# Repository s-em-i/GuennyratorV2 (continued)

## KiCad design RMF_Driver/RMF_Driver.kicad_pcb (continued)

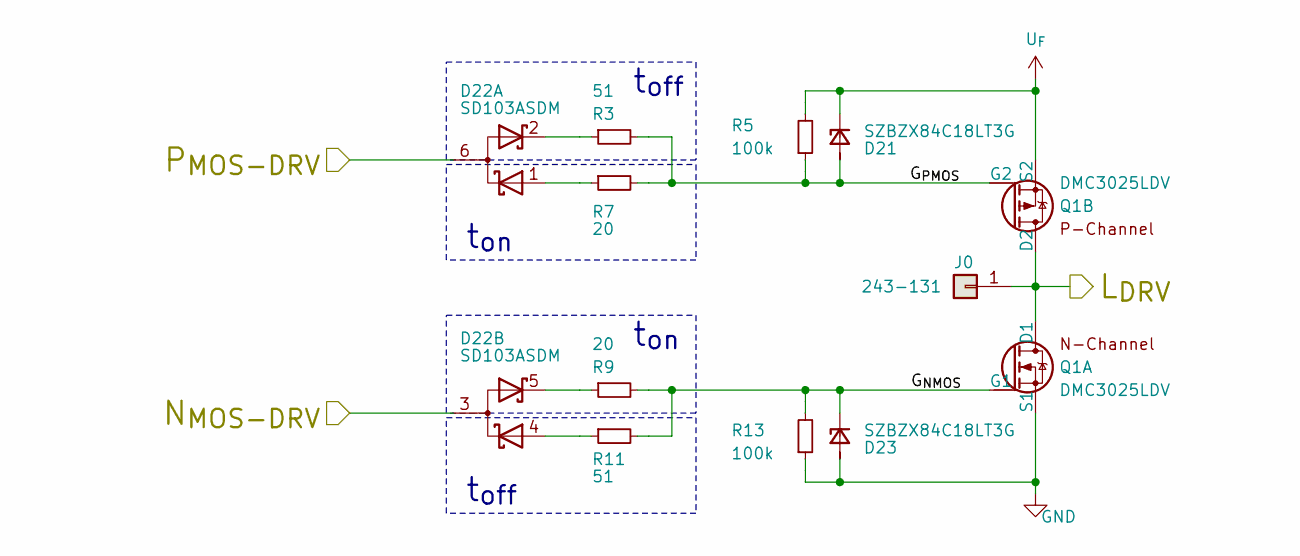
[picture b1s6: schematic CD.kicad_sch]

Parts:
D21, D23: SZBZX84C18LT3G; SOT-23; MPN 1 SZBZX84C18LT3G
D22: SD103ASDM; SOT-23-6; MPN 1 SD103ASDM-7-F
J0: 243-131; MPN 1 243-131
Q1: DMC3025LDV; Diodes_PowerDI3333-8_TypeUXC; MPN 1 DMC3025LDV
R3, R11: 51; R_0402_1005Metric; MPN 1 AC0402FR-0751RL
R5, R13: 100k; R_0402_1005Metric; MPN 1 AC0402FR-13100KL
R7, R9: 20; R_0402_1005Metric; MPN 1 AC0402FR-0720RL

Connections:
/Mosfet Coil Driver/CD1/G_{NMOS}: D23.3 (K), Q1.2 (G1), R9.2, R11.2, R13.2
/Mosfet Coil Driver/CD1/G_{PMOS}: D21.1 (A), D21.2 (A), Q1.4 (G2), R3.2, R5.1, R7.2
/Mosfet Coil Driver/CD1/N_{MOS-DRV}: D22.3 (AK2); also elsewhere on the board
/Mosfet Coil Driver/CD1/P_{MOS-DRV}: D22.6 (AK1); also elsewhere on the board
GND: D23.1 (A), D23.2 (A), Q1.1 (S1), R13.1; also elsewhere on the board
L_{0}-L_{1}: J0.1 (Pin_1_1), Q1.5 (D2), Q1.8 (D1)
unnamed: D22.1 (A1), R7.1
unnamed: D22.2 (K1), R3.1
unnamed: D22.4 (A1), R11.1
unnamed: D22.5 (K2), R9.1
U_{F}: D21.3 (K), Q1.3 (S2), R5.2; also elsewhere on the board

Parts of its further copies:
D24, D26, D27, D29, D30, D32, D33, D35, D36, D38, D39, D41, D42, D44, D45, D47, D48, D50, D51, D53, D54, D56, D57, D59, D60, D62, D63, D65, D66, D68, D69, D71, D72, D74: SZBZX84C18LT3G; SOT-23; MPN 1 SZBZX84C18LT3G
D25, D28, D31, D34, D37, D40, D43, D46, D49, D52, D55, D58, D61, D64, D67, D70, D73: SD103ASDM; SOT-23-6; MPN 1 SD103ASDM-7-F
J1, J2, J3, J4, J5, J6, J7, J8, J9, J10, J11, J12, J13, J14, J15, J16, J17: 243-131; MPN 1 243-131
Q0, Q2, Q3, Q4, Q5, Q6, Q7, Q8, Q9, Q10, Q11, Q12, Q13, Q14, Q15, Q16, Q17: DMC3025LDV; Diodes_PowerDI3333-8_TypeUXC; MPN 1 DMC3025LDV
R15, R23, R27, R35, R39, R43, R45, R49, R51, R55, R57, R61, R63, R67, R69, R73, R75, R79, R81, R85, R87, R91, R93, R97, R99, R103, R105, R109, R111, R115, R117, R121, R123, R127: 51; R_0402_1005Metric; MPN 1 AC0402FR-0751RL
R17, R25, R29, R37, R40, R44, R46, R50, R52, R56, R58, R62, R64, R68, R70, R74, R76, R80, R82, R86, R88, R92, R94, R98, R100, R104, R106, R110, R112, R116, R118, R122, R124, R128: 100k; R_0402_1005Metric; MPN 1 AC0402FR-13100KL
R19, R21, R31, R33, R41, R42, R47, R48, R53, R54, R59, R60, R65, R66, R71, R72, R77, R78, R83, R84, R89, R90, R95, R96, R101, R102, R107, R108, R113, R114, R119, R120, R125, R126: 20; R_0402_1005Metric; MPN 1 AC0402FR-0720RL

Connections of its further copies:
/Mosfet Coil Driver/CD0/G_{NMOS}: D26.3 (K), Q0.2 (G1), R21.2, R23.2, R25.2
/Mosfet Coil Driver/CD0/G_{PMOS}: D24.1 (A), D24.2 (A), Q0.4 (G2), R15.2, R17.1, R19.2
/Mosfet Coil Driver/CD0/N_{MOS-DRV}: D25.3 (AK2), D52.3 (AK2); also elsewhere on the board
/Mosfet Coil Driver/CD0/P_{MOS-DRV}: D25.6 (AK1), D52.6 (AK1); also elsewhere on the board
/Mosfet Coil Driver/CD1/N_{MOS-DRV}: D55.3 (AK2); also elsewhere on the board
/Mosfet Coil Driver/CD1/P_{MOS-DRV}: D55.6 (AK1); also elsewhere on the board
/Mosfet Coil Driver/CD2/G_{NMOS}: D29.3 (K), Q2.2 (G1), R33.2, R35.2, R37.2
/Mosfet Coil Driver/CD2/G_{PMOS}: D27.1 (A), D27.2 (A), Q2.4 (G2), R27.2, R29.1, R31.2
/Mosfet Coil Driver/CD3/G_{NMOS}: D32.3 (K), Q3.2 (G1), R42.2, R43.2, R44.2
/Mosfet Coil Driver/CD3/G_{PMOS}: D30.1 (A), D30.2 (A), Q3.4 (G2), R39.2, R40.1, R41.2
/Mosfet Coil Driver/CD4/G_{NMOS}: D35.3 (K), Q4.2 (G1), R48.2, R49.2, R50.2
/Mosfet Coil Driver/CD4/G_{PMOS}: D33.1 (A), D33.2 (A), Q4.4 (G2), R45.2, R46.1, R47.2
/Mosfet Coil Driver/CD5/G_{NMOS}: D38.3 (K), Q5.2 (G1), R54.2, R55.2, R56.2
/Mosfet Coil Driver/CD5/G_{PMOS}: D36.1 (A), D36.2 (A), Q5.4 (G2), R51.2, R52.1, R53.2
/Mosfet Coil Driver/CD6/G_{NMOS}: D41.3 (K), Q6.2 (G1), R60.2, R61.2, R62.2
/Mosfet Coil Driver/CD6/G_{PMOS}: D39.1 (A), D39.2 (A), Q6.4 (G2), R57.2, R58.1, R59.2
/Mosfet Coil Driver/CD7/G_{NMOS}: D44.3 (K), Q7.2 (G1), R66.2, R67.2, R68.2
/Mosfet Coil Driver/CD7/G_{PMOS}: D42.1 (A), D42.2 (A), Q7.4 (G2), R63.2, R64.1, R65.2
/Mosfet Coil Driver/CD8/G_{NMOS}: D47.3 (K), Q8.2 (G1), R72.2, R73.2, R74.2
/Mosfet Coil Driver/CD8/G_{PMOS}: D45.1 (A), D45.2 (A), Q8.4 (G2), R69.2, R70.1, R71.2
/Mosfet Coil Driver/CD9/G_{NMOS}: D53.3 (K), Q9.2 (G1), R84.2, R85.2, R86.2
/Mosfet Coil Driver/CD9/G_{PMOS}: D51.1 (A), D51.2 (A), Q9.4 (G2), R81.2, R82.1, R83.2
/Mosfet Coil Driver/CD10/G_{NMOS}: D56.3 (K), Q10.2 (G1), R90.2, R91.2, R92.2
/Mosfet Coil Driver/CD10/G_{PMOS}: D54.1 (A), D54.2 (A), Q10.4 (G2), R87.2, R88.1, R89.2
/Mosfet Coil Driver/CD11/G_{NMOS}: D50.3 (K), Q11.2 (G1), R78.2, R79.2, R80.2
/Mosfet Coil Driver/CD11/G_{PMOS}: D48.1 (A), D48.2 (A), Q11.4 (G2), R75.2, R76.1, R77.2
/Mosfet Coil Driver/CD11/N_{MOS-DRV}: D28.3 (AK2), D49.3 (AK2); also elsewhere on the board
/Mosfet Coil Driver/CD11/P_{MOS-DRV}: D28.6 (AK1), D49.6 (AK1); also elsewhere on the board
/Mosfet Coil Driver/CD12/G_{NMOS}: D74.3 (K), Q12.2 (G1), R126.2, R127.2, R128.2
/Mosfet Coil Driver/CD12/G_{PMOS}: D72.1 (A), D72.2 (A), Q12.4 (G2), R123.2, R124.1, R125.2
/Mosfet Coil Driver/CD12/N_{MOS-DRV}: D31.3 (AK2), D73.3 (AK2); also elsewhere on the board
/Mosfet Coil Driver/CD12/P_{MOS-DRV}: D31.6 (AK1), D73.6 (AK1); also elsewhere on the board
/Mosfet Coil Driver/CD13/G_{NMOS}: D62.3 (K), Q13.2 (G1), R102.2, R103.2, R104.2
/Mosfet Coil Driver/CD13/G_{PMOS}: D60.1 (A), D60.2 (A), Q13.4 (G2), R99.2, R100.1, R101.2
/Mosfet Coil Driver/CD13/N_{MOS-DRV}: D34.3 (AK2), D61.3 (AK2); also elsewhere on the board
/Mosfet Coil Driver/CD13/P_{MOS-DRV}: D34.6 (AK1), D61.6 (AK1); also elsewhere on the board
/Mosfet Coil Driver/CD14/G_{NMOS}: D68.3 (K), Q14.2 (G1), R114.2, R115.2, R116.2
/Mosfet Coil Driver/CD14/G_{PMOS}: D66.1 (A), D66.2 (A), Q14.4 (G2), R111.2, R112.1, R113.2
/Mosfet Coil Driver/CD14/N_{MOS-DRV}: D37.3 (AK2), D67.3 (AK2); also elsewhere on the board
/Mosfet Coil Driver/CD14/P_{MOS-DRV}: D37.6 (AK1), D67.6 (AK1); also elsewhere on the board
/Mosfet Coil Driver/CD15/G_{NMOS}: D71.3 (K), Q15.2 (G1), R120.2, R121.2, R122.2
/Mosfet Coil Driver/CD15/G_{PMOS}: D69.1 (A), D69.2 (A), Q15.4 (G2), R117.2, R118.1, R119.2
/Mosfet Coil Driver/CD15/N_{MOS-DRV}: D40.3 (AK2), D70.3 (AK2); also elsewhere on the board
/Mosfet Coil Driver/CD15/P_{MOS-DRV}: D40.6 (AK1), D70.6 (AK1); also elsewhere on the board
/Mosfet Coil Driver/CD16/G_{NMOS}: D59.3 (K), Q16.2 (G1), R96.2, R97.2, R98.2
/Mosfet Coil Driver/CD16/G_{PMOS}: D57.1 (A), D57.2 (A), Q16.4 (G2), R93.2, R94.1, R95.2
/Mosfet Coil Driver/CD16/N_{MOS-DRV}: D43.3 (AK2), D58.3 (AK2); also elsewhere on the board
/Mosfet Coil Driver/CD16/P_{MOS-DRV}: D43.6 (AK1), D58.6 (AK1); also elsewhere on the board
/Mosfet Coil Driver/CD17/G_{NMOS}: D65.3 (K), Q17.2 (G1), R108.2, R109.2, R110.2
/Mosfet Coil Driver/CD17/G_{PMOS}: D63.1 (A), D63.2 (A), Q17.4 (G2), R105.2, R106.1, R107.2
/Mosfet Coil Driver/CD17/N_{MOS-DRV}: D46.3 (AK2), D64.3 (AK2); also elsewhere on the board
/Mosfet Coil Driver/CD17/P_{MOS-DRV}: D46.6 (AK1), D64.6 (AK1); also elsewhere on the board
GND: D26.1 (A), D26.2 (A), D29.1 (A), D29.2 (A), D32.1 (A), D32.2 (A), D35.1 (A), D35.2 (A), D38.1 (A), D38.2 (A), D41.1 (A), D41.2 (A), D44.1 (A), D44.2 (A), D47.1 (A), D47.2 (A), D50.1 (A), D50.2 (A), D53.1 (A), D53.2 (A), D56.1 (A), D56.2 (A), D59.1 (A), D59.2 (A), D62.1 (A), D62.2 (A), D65.1 (A), D65.2 (A), D68.1 (A), D68.2 (A), D71.1 (A), D71.2 (A), D74.1 (A), D74.2 (A), Q0.1 (S1), Q2.1 (S1), Q3.1 (S1), Q4.1 (S1), Q5.1 (S1), Q6.1 (S1), Q7.1 (S1), Q8.1 (S1), Q9.1 (S1), Q10.1 (S1), Q11.1 (S1), Q12.1 (S1), Q13.1 (S1), Q14.1 (S1), Q15.1 (S1), Q16.1 (S1), Q17.1 (S1), R25.1, R37.1, R44.1, R50.1, R56.1, R62.1, R68.1, R74.1, R80.1, R86.1, R92.1, R98.1, R104.1, R110.1, R116.1, R122.1, R128.1; also elsewhere on the board
L_{1}-L_{2}: J1.1 (Pin_1_1), Q2.5 (D2), Q2.8 (D1)
L_{2}-L_{3}: J2.1 (Pin_1_1), Q3.5 (D2), Q3.8 (D1)
L_{3}-L_{4}: J3.1 (Pin_1_1), Q4.5 (D2), Q4.8 (D1)
L_{4}-L_{5}: J4.1 (Pin_1_1), Q5.5 (D2), Q5.8 (D1)
L_{5}-L_{6}: J5.1 (Pin_1_1), Q6.5 (D2), Q6.8 (D1)
L_{6}-L_{7}: J6.1 (Pin_1_1), Q7.5 (D2), Q7.8 (D1)
L_{7}-L_{8}: J7.1 (Pin_1_1), Q8.5 (D2), Q8.8 (D1)
L_{8}-L_{9}: J8.1 (Pin_1_1), Q9.5 (D2), Q9.8 (D1)
L_{9}-L_{10}: J9.1 (Pin_1_1), Q10.5 (D2), Q10.8 (D1)
L_{10}-L_{11}: J10.1 (Pin_1_1), Q11.5 (D2), Q11.8 (D1)
L_{11}-L_{12}: J11.1 (Pin_1_1), Q12.5 (D2), Q12.8 (D1)
L_{12}-L_{13}: J12.1 (Pin_1_1), Q13.5 (D2), Q13.8 (D1)
L_{13}-L_{14}: J13.1 (Pin_1_1), Q14.5 (D2), Q14.8 (D1)
L_{14}-L_{15}: J14.1 (Pin_1_1), Q15.5 (D2), Q15.8 (D1)
L_{15}-L_{16}: J15.1 (Pin_1_1), Q16.5 (D2), Q16.8 (D1)
L_{16}-L_{17}: J16.1 (Pin_1_1), Q17.5 (D2), Q17.8 (D1)
L_{17}-L_{0}: J17.1 (Pin_1_1), Q0.5 (D2), Q0.8 (D1)
unnamed: D25.1 (A1), R19.1
unnamed: D25.2 (K1), R15.1
unnamed: D25.4 (A1), R23.1
unnamed: D25.5 (K2), R21.1
unnamed: D28.1 (A1), R31.1
unnamed: D28.2 (K1), R27.1
unnamed: D28.4 (A1), R35.1
unnamed: D28.5 (K2), R33.1
unnamed: D31.1 (A1), R41.1
unnamed: D31.2 (K1), R39.1
unnamed: D31.4 (A1), R43.1
unnamed: D31.5 (K2), R42.1
unnamed: D34.1 (A1), R47.1
unnamed: D34.2 (K1), R45.1
unnamed: D34.4 (A1), R49.1
unnamed: D34.5 (K2), R48.1
unnamed: D37.1 (A1), R53.1
unnamed: D37.2 (K1), R51.1
unnamed: D37.4 (A1), R55.1
unnamed: D37.5 (K2), R54.1
unnamed: D40.1 (A1), R59.1
unnamed: D40.2 (K1), R57.1
unnamed: D40.4 (A1), R61.1
unnamed: D40.5 (K2), R60.1
unnamed: D43.1 (A1), R65.1
unnamed: D43.2 (K1), R63.1
unnamed: D43.4 (A1), R67.1
unnamed: D43.5 (K2), R66.1
unnamed: D46.1 (A1), R71.1
unnamed: D46.2 (K1), R69.1
unnamed: D46.4 (A1), R73.1
unnamed: D46.5 (K2), R72.1
unnamed: D49.1 (A1), R77.1
unnamed: D49.2 (K1), R75.1
unnamed: D49.4 (A1), R79.1
unnamed: D49.5 (K2), R78.1
unnamed: D52.1 (A1), R83.1
unnamed: D52.2 (K1), R81.1
unnamed: D52.4 (A1), R85.1
unnamed: D52.5 (K2), R84.1
unnamed: D55.1 (A1), R89.1
unnamed: D55.2 (K1), R87.1
unnamed: D55.4 (A1), R91.1
unnamed: D55.5 (K2), R90.1
unnamed: D58.1 (A1), R95.1
unnamed: D58.2 (K1), R93.1
unnamed: D58.4 (A1), R97.1
unnamed: D58.5 (K2), R96.1
unnamed: D61.1 (A1), R101.1
unnamed: D61.2 (K1), R99.1
unnamed: D61.4 (A1), R103.1
unnamed: D61.5 (K2), R102.1
unnamed: D64.1 (A1), R107.1
unnamed: D64.2 (K1), R105.1
unnamed: D64.4 (A1), R109.1
unnamed: D64.5 (K2), R108.1
unnamed: D67.1 (A1), R113.1
unnamed: D67.2 (K1), R111.1
unnamed: D67.4 (A1), R115.1
unnamed: D67.5 (K2), R114.1
unnamed: D70.1 (A1), R119.1
unnamed: D70.2 (K1), R117.1
unnamed: D70.4 (A1), R121.1
unnamed: D70.5 (K2), R120.1
unnamed: D73.1 (A1), R125.1
unnamed: D73.2 (K1), R123.1
unnamed: D73.4 (A1), R127.1
unnamed: D73.5 (K2), R126.1
U_{F}: D24.3 (K), D27.3 (K), D30.3 (K), D33.3 (K), D36.3 (K), D39.3 (K), D42.3 (K), D45.3 (K), D48.3 (K), D51.3 (K), D54.3 (K), D57.3 (K), D60.3 (K), D63.3 (K), D66.3 (K), D69.3 (K), D72.3 (K), Q0.3 (S2), Q2.3 (S2), Q3.3 (S2), Q4.3 (S2), Q5.3 (S2), Q6.3 (S2), Q7.3 (S2), Q8.3 (S2), Q9.3 (S2), Q10.3 (S2), Q11.3 (S2), Q12.3 (S2), Q13.3 (S2), Q14.3 (S2), Q15.3 (S2), Q16.3 (S2), Q17.3 (S2), R17.2, R29.2, R40.2, R46.2, R52.2, R58.2, R64.2, R70.2, R76.2, R82.2, R88.2, R94.2, R100.2, R106.2, R112.2, R118.2, R124.2; also elsewhere on the board

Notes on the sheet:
t_{on}
t_{off}

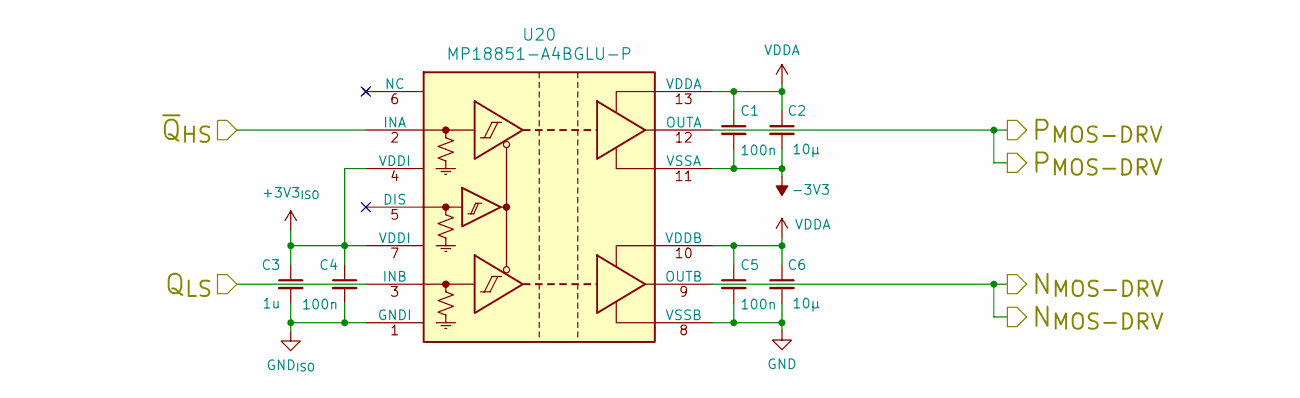
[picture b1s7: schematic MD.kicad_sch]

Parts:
C1, C4, C5: 100n; C_0402_1005Metric; MPN 1 CL05B104KB54PNC
C2, C6: 10µ; C_0805_2012Metric; MPN 1 CL21B106KAYQNNE
C3: 1u; C_0603_1608Metric; MPN 1 CL10B105KB8NQNC
U20: MP18851-A4BGLU-P; LGA-13_MP18851_MNP-L; MPN 1 MP18851-A4BGLU-P

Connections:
+3V3_{ISO}: C3.1, C4.1, U20.4 (VDDI), U20.7 (VDDI); also elsewhere on the board
-3V3: C1.2, C2.2, U20.11 (VSSA); also elsewhere on the board
/Mosfet Coil Driver/CD0/N_{MOS-DRV}: U20.9 (OUTB); also elsewhere on the board
/Mosfet Coil Driver/CD0/P_{MOS-DRV}: U20.12 (OUTA); also elsewhere on the board
GND: C5.2, C6.2, U20.8 (VSSB); also elsewhere on the board
GND_{ISO}: C3.2, C4.2, U20.1 (GNDI); also elsewhere on the board
Q_{4}: U20.3 (INB); also elsewhere on the board
VDDA: C1.1, C2.1, C5.1, C6.1, U20.10 (VDDB), U20.13 (VDDA); also elsewhere on the board
~Q_{0}: U20.2 (INA); also elsewhere on the board

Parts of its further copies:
C62, C65, C66, C68, C71, C72, C74, C77, C78, C80, C83, C84, C86, C89, C90, C92, C95, C96, C98, C101, C102, C104, C107, C108: 100n; C_0402_1005Metric; MPN 1 CL05B104KB54PNC
C63, C67, C69, C73, C75, C79, C81, C85, C87, C91, C93, C97, C99, C103, C105, C109: 10µ; C_0805_2012Metric; MPN 1 CL21B106KAYQNNE
C64, C70, C76, C82, C88, C94, C100, C106: 1u; C_0603_1608Metric; MPN 1 CL10B105KB8NQNC
U21, U22, U23, U24, U25, U26, U27, U28: MP18851-A4BGLU-P; LGA-13_MP18851_MNP-L; MPN 1 MP18851-A4BGLU-P

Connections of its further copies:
+3V3_{ISO}: C64.1, C65.1, C70.1, C71.1, C76.1, C77.1, C82.1, C83.1, C88.1, C89.1, C94.1, C95.1, C100.1, C101.1, C106.1, C107.1, U21.4 (VDDI), U21.7 (VDDI), U22.4 (VDDI), U22.7 (VDDI), U23.4 (VDDI), U23.7 (VDDI), U24.4 (VDDI), U24.7 (VDDI), U25.4 (VDDI), U25.7 (VDDI), U26.4 (VDDI), U26.7 (VDDI), U27.4 (VDDI), U27.7 (VDDI), U28.4 (VDDI), U28.7 (VDDI); also elsewhere on the board
-3V3: C62.2, C63.2, C68.2, C69.2, C74.2, C75.2, C80.2, C81.2, C86.2, C87.2, C92.2, C93.2, C98.2, C99.2, C104.2, C105.2, U21.11 (VSSA), U22.11 (VSSA), U23.11 (VSSA), U24.11 (VSSA), U25.11 (VSSA), U26.11 (VSSA), U27.11 (VSSA), U28.11 (VSSA); also elsewhere on the board
/Mosfet Coil Driver/CD1/N_{MOS-DRV}: U21.9 (OUTB); also elsewhere on the board
/Mosfet Coil Driver/CD1/P_{MOS-DRV}: U21.12 (OUTA); also elsewhere on the board
/Mosfet Coil Driver/CD11/N_{MOS-DRV}: U22.9 (OUTB); also elsewhere on the board
/Mosfet Coil Driver/CD11/P_{MOS-DRV}: U22.12 (OUTA); also elsewhere on the board
/Mosfet Coil Driver/CD12/N_{MOS-DRV}: U23.9 (OUTB); also elsewhere on the board
/Mosfet Coil Driver/CD12/P_{MOS-DRV}: U23.12 (OUTA); also elsewhere on the board
/Mosfet Coil Driver/CD13/N_{MOS-DRV}: U24.9 (OUTB); also elsewhere on the board
/Mosfet Coil Driver/CD13/P_{MOS-DRV}: U24.12 (OUTA); also elsewhere on the board
/Mosfet Coil Driver/CD14/N_{MOS-DRV}: U25.9 (OUTB); also elsewhere on the board
/Mosfet Coil Driver/CD14/P_{MOS-DRV}: U25.12 (OUTA); also elsewhere on the board
/Mosfet Coil Driver/CD15/N_{MOS-DRV}: U26.9 (OUTB); also elsewhere on the board
/Mosfet Coil Driver/CD15/P_{MOS-DRV}: U26.12 (OUTA); also elsewhere on the board
/Mosfet Coil Driver/CD16/N_{MOS-DRV}: U27.9 (OUTB); also elsewhere on the board
/Mosfet Coil Driver/CD16/P_{MOS-DRV}: U27.12 (OUTA); also elsewhere on the board
/Mosfet Coil Driver/CD17/N_{MOS-DRV}: U28.9 (OUTB); also elsewhere on the board
/Mosfet Coil Driver/CD17/P_{MOS-DRV}: U28.12 (OUTA); also elsewhere on the board
GND: C66.2, C67.2, C72.2, C73.2, C78.2, C79.2, C84.2, C85.2, C90.2, C91.2, C96.2, C97.2, C102.2, C103.2, C108.2, C109.2, U21.8 (VSSB), U22.8 (VSSB), U23.8 (VSSB), U24.8 (VSSB), U25.8 (VSSB), U26.8 (VSSB), U27.8 (VSSB), U28.8 (VSSB); also elsewhere on the board
GND_{ISO}: C64.2, C65.2, C70.2, C71.2, C76.2, C77.2, C82.2, C83.2, C88.2, C89.2, C94.2, C95.2, C100.2, C101.2, C106.2, C107.2, U21.1 (GNDI), U22.1 (GNDI), U23.1 (GNDI), U24.1 (GNDI), U25.1 (GNDI), U26.1 (GNDI), U27.1 (GNDI), U28.1 (GNDI); also elsewhere on the board
Q_{0}: U25.3 (INB); also elsewhere on the board
Q_{1}: U26.3 (INB); also elsewhere on the board
Q_{2}: U27.3 (INB); also elsewhere on the board
Q_{3}: U28.3 (INB); also elsewhere on the board
Q_{5}: U21.3 (INB); also elsewhere on the board
Q_{6}: U22.3 (INB); also elsewhere on the board
Q_{7}: U23.3 (INB); also elsewhere on the board
Q_{8}: U24.3 (INB); also elsewhere on the board
VDDA: C62.1, C63.1, C66.1, C67.1, C68.1, C69.1, C72.1, C73.1, C74.1, C75.1, C78.1, C79.1, C80.1, C81.1, C84.1, C85.1, C86.1, C87.1, C90.1, C91.1, C92.1, C93.1, C96.1, C97.1, C98.1, C99.1, C102.1, C103.1, C104.1, C105.1, C108.1, C109.1, U21.10 (VDDB), U21.13 (VDDA), U22.10 (VDDB), U22.13 (VDDA), U23.10 (VDDB), U23.13 (VDDA), U24.10 (VDDB), U24.13 (VDDA), U25.10 (VDDB), U25.13 (VDDA), U26.10 (VDDB), U26.13 (VDDA), U27.10 (VDDB), U27.13 (VDDA), U28.10 (VDDB), U28.13 (VDDA); also elsewhere on the board
~Q_{1}: U21.2 (INA); also elsewhere on the board
~Q_{2}: U22.2 (INA); also elsewhere on the board
~Q_{3}: U23.2 (INA); also elsewhere on the board
~Q_{4}: U24.2 (INA); also elsewhere on the board
~Q_{5}: U25.2 (INA); also elsewhere on the board
~Q_{6}: U26.2 (INA); also elsewhere on the board
~Q_{7}: U27.2 (INA); also elsewhere on the board
~Q_{8}: U28.2 (INA); also elsewhere on the board

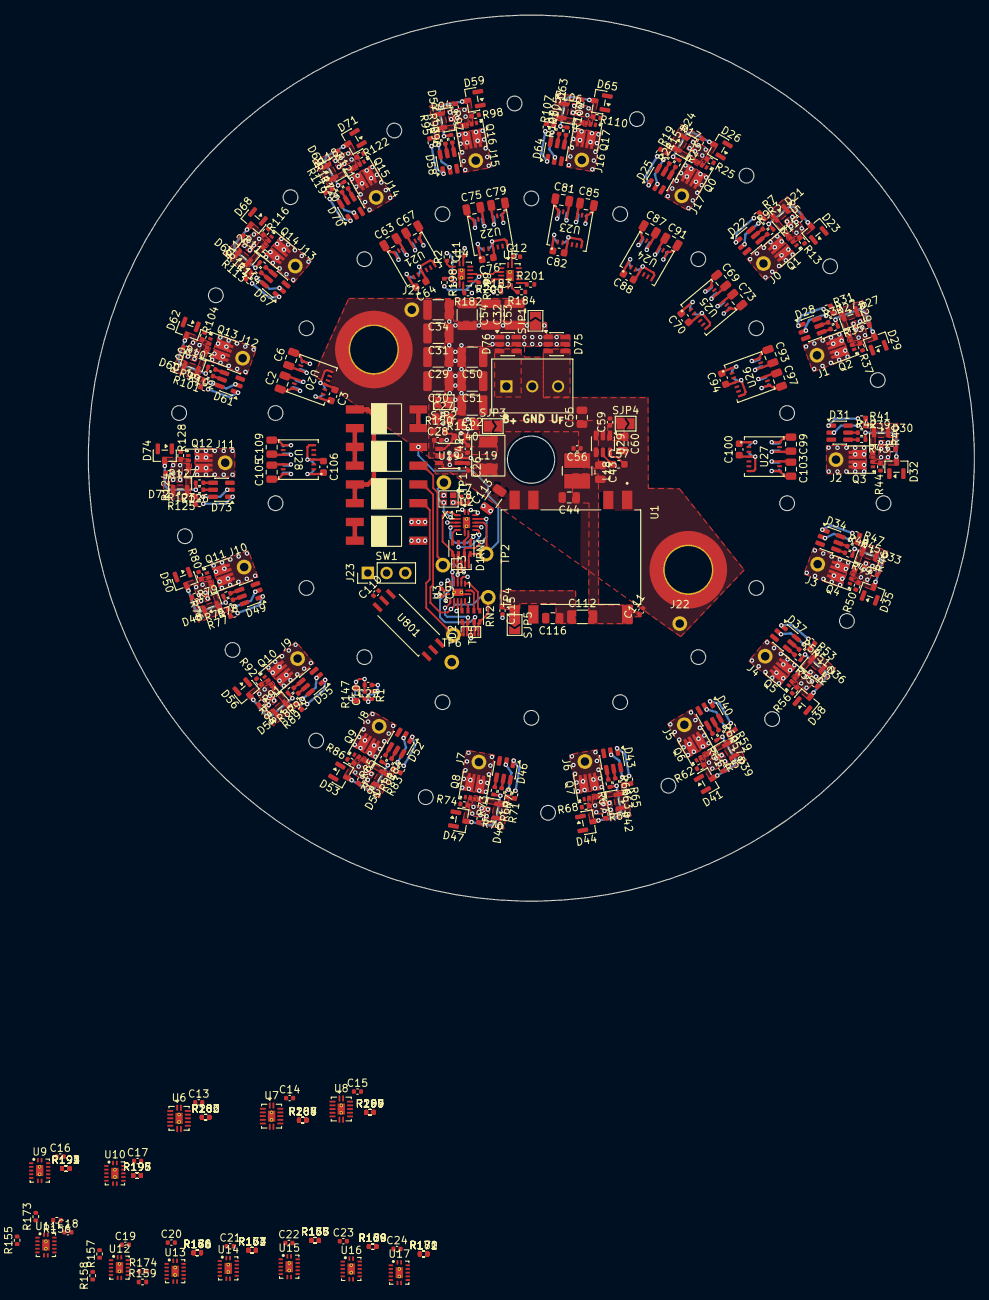
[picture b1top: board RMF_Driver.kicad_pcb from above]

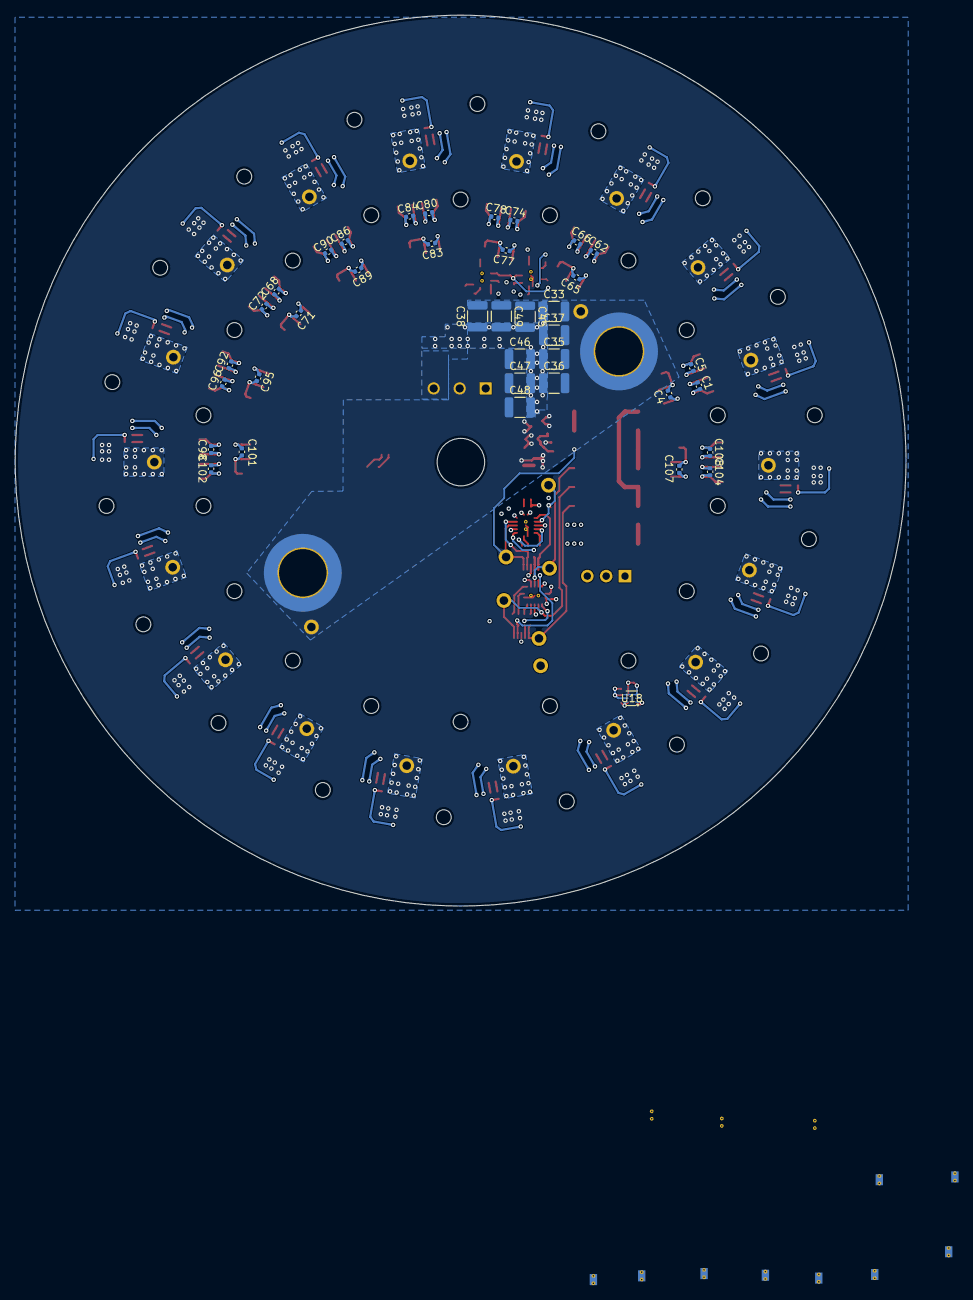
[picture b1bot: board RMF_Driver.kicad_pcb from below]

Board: 4 copper layers, 120.0 x 120.0 mm, 424 parts (38 on the bottom side), 296 nets.
